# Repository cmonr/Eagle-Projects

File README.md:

Eagle-Projects
==============

Various Eagle Projects I work on

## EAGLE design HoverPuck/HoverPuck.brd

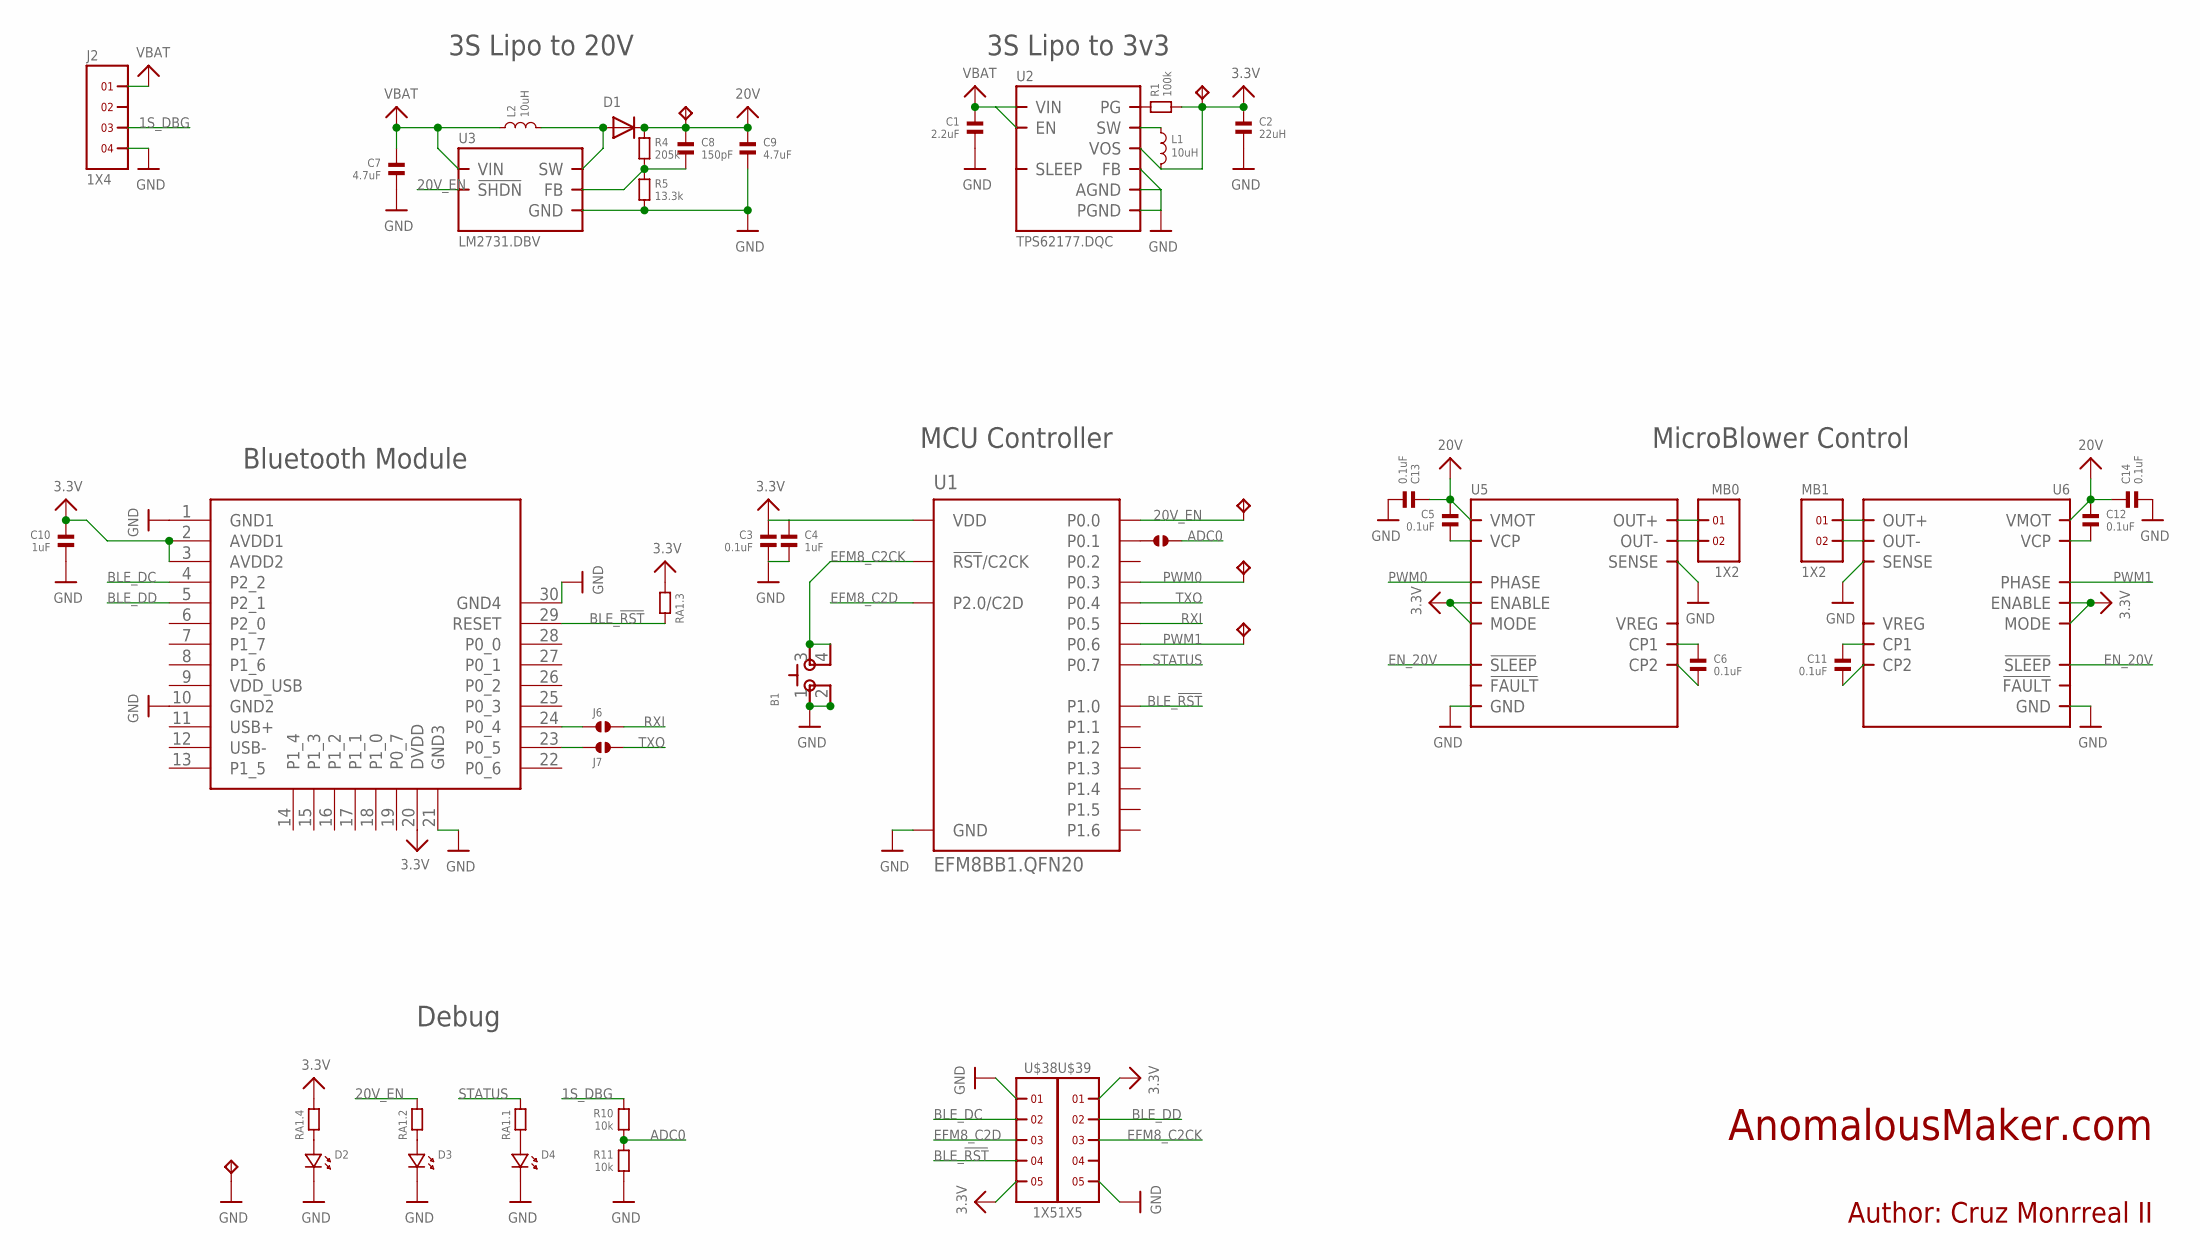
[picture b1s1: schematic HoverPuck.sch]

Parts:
B1: SKSCLDE010
C1: 2.2uF; 0603
C2: 22uH; 0805
C3, C5, C6, C11, C12, C13, C14: 0.1uF; 0603
C4, C10: 1uF; 0603
C7, C9: 4.7uF; 0805
C8: 150pF; 0603
D1: MBR0530T1G; SOD-123
D2, D3, D4: LED.0603; 0603.LED
J1, J6, J7: SOLDERJUMPER.2.SML.PASTE; 2.SML.PASTE
J2: 1X4
L1: 10uH; LPS4018
L2: 10uH; SRN6045
MB0, MB1: 1X2
R1: 100k; 0603
R4: 205k; 0603
R5: 13.3k; 0603
R10, R11: 10k; 0603
RA1: RA-4.0603; 0603.4.C
TP1, TP2, TP3, TP4, TP5, TP6: TPTP06R; TP06R
U1: EFM8BB1.QFN20; QFN20
U2: TPS62177.DQC; DQC
U3: LM2731.DBV; DBV.5
U4: BLE112-A
U5, U6: DRV8800.RTY; RTY.16
U$38, U$39: 1X5

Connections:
1S_DBG: J2.3, R10.1
3.3V: C2.1, C3.1, C4.1, C10.1, L1.2, R1.2, RA1.6 (2), RA1.8 (2), TP1.TP, U1.4 (VDD), U2.10 (VOS), U4.2 (AVDD1), U4.3 (AVDD2), U4.20 (DVDD), U5.4 (ENABLE), U5.16 (MODE), U6.4 (ENABLE), U6.16 (MODE), U$38.5, U$39.1
12V: C5.1, C12.1, C13.1, C14.1, U5.8 (VMOT), U6.8 (VMOT)
20V: C8.1, C9.1, D1.C, R4.1, TP2.TP
20V_EN: RA1.4 (2), TP5.TP, U1.2 (P0.0), U3.4 (!SHDN)
ADC0: J1.2, R10.2, R11.1
BLE_!RST: RA1.5 (1), U1.14 (P1.0), U4.29 (RESET), U$38.4
BLE_DC: U4.4 (P2_2), U$38.2
BLE_DD: U4.5 (P2_1), U$39.2
EFM8_C2CK: B1.3 (4), B1.4 (3), U1.5 (!RST!/C2CK), U$39.3
EFM8_C2D: U1.6 (P2.0/C2D), U$38.3
EN_20V: U5.3 (!SLEEP), U6.3 (!SLEEP)
GND: B1.1, B1.2, C1.2, C2.2, C3.2, C4.2, C7.2, C9.2, C10.2, C13.2, C14.2, D2.P$2 (2), D3.P$2 (2), D4.P$2 (2), J2.4, R5.2, R11.2, TP6.TP, U1.3 (GND), U1.12 (GND), U1.PAD (GND), U2.1 (PGND), U2.5 (FB), U2.6 (AGND), U2.PAD (PGND), U3.2 (GND), U4.1 (GND1), U4.10 (GND2), U4.21 (GND3), U4.30 (GND4), U5.2 (GND), U5.7 (SENSE), U5.12 (GND), U5.PAD (GND), U6.2 (GND), U6.7 (SENSE), U6.12 (GND), U6.PAD (GND), U$38.1, U$39.5
unnamed: C12.2, U6.13 (VCP)
unnamed: C5.2, U5.13 (VCP)
unnamed: L1.1, U2.9 (SW)
unnamed: D2.P$1 (1), RA1.7 (1)
unnamed: D1.A, L2.2, U3.1 (SW)
unnamed: R1.1, U2.7 (PG)
unnamed: C8.2, R4.2, R5.1, U3.3 (FB)
unnamed: D4.P$1 (1), RA1.1
unnamed: D3.P$1 (1), RA1.3 (1)
unnamed: J6.1, U4.24 (P0_4)
unnamed: J7.1, U4.23 (P0_5)
unnamed: J1.1, U1.1 (P0.1)
unnamed: MB0.1, U5.6 (OUT+)
unnamed: MB0.2, U5.9 (OUT-)
unnamed: MB1.1, U6.6 (OUT+)
unnamed: MB1.2, U6.9 (OUT-)
unnamed: C6.1, U5.10 (CP1)
unnamed: C6.2, U5.11 (CP2)
unnamed: C11.2, U6.11 (CP2)
unnamed: C11.1, U6.10 (CP1)
PWM0: TP3.TP, U1.19 (P0.3), U5.1 (PHASE)
PWM1: TP4.TP, U1.16 (P0.6), U6.1 (PHASE)
RXI: J6.2, U1.17 (P0.5)
STATUS: RA1.2, U1.15 (P0.7)
TXO: J7.2, U1.18 (P0.4)
VBAT: C1.1, C7.1, J2.1, L2.1, U2.2 (VIN), U2.3 (EN), U3.5 (VIN)

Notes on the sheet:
3S Lipo to 3v3
MCU Controller
3S Lipo to 20V
Bluetooth Module
MicroBlower Control
Debug
Author: Cruz Monrreal II
AnomalousMaker.com

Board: 2 copper layers, 47 parts (5 on the bottom side), 39 nets, no tracks yet.

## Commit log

2014-05-25 Added submodules to Eagle-Projects
2014-05-25 Added Eagle-Libraries to Eagle-Projects directory (imo, easier to work with in this config)
2014-05-27 Renamed Eagle Libraries directory
2014-05-28 Updated BoM for Robotics BoosterPack
2015-03-18 Created HoverPuck project
2015-03-18 Pushing changes to Libraries
2015-03-19 Schematic seems about done and layout of components looks promising Next step will be the actual routing
2015-03-19 A majority of routing completed. Switching regulators now completed. Minor MCU signals still needed, as well as labeling.
2015-03-19 Updated TODO list
    Added more references on what signals to breakout for BLE112
2015-03-19 Updated board file with more routing and placement
2015-03-19 Added single debugger connector
    Replaced 1k resistors with resistor array
2015-03-21 Completed v1 of HoverPuck PCB
2015-04-09 Started v2 of the HoverPuck. Changed driver circuit, and moving things around. New driver circuit still needs to be confirmed functional.
2015-04-09 Moved HoverPuck into its own repo

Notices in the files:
parts and their libraries:
microbuilder: This work is placed in the public domain, and may be freely used for commercial and non-commercial work with the following conditions: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
SparkFun-RF: Licensing: CC v3.0 Share-Alike You are welcome to use this library for commercial purposes.
